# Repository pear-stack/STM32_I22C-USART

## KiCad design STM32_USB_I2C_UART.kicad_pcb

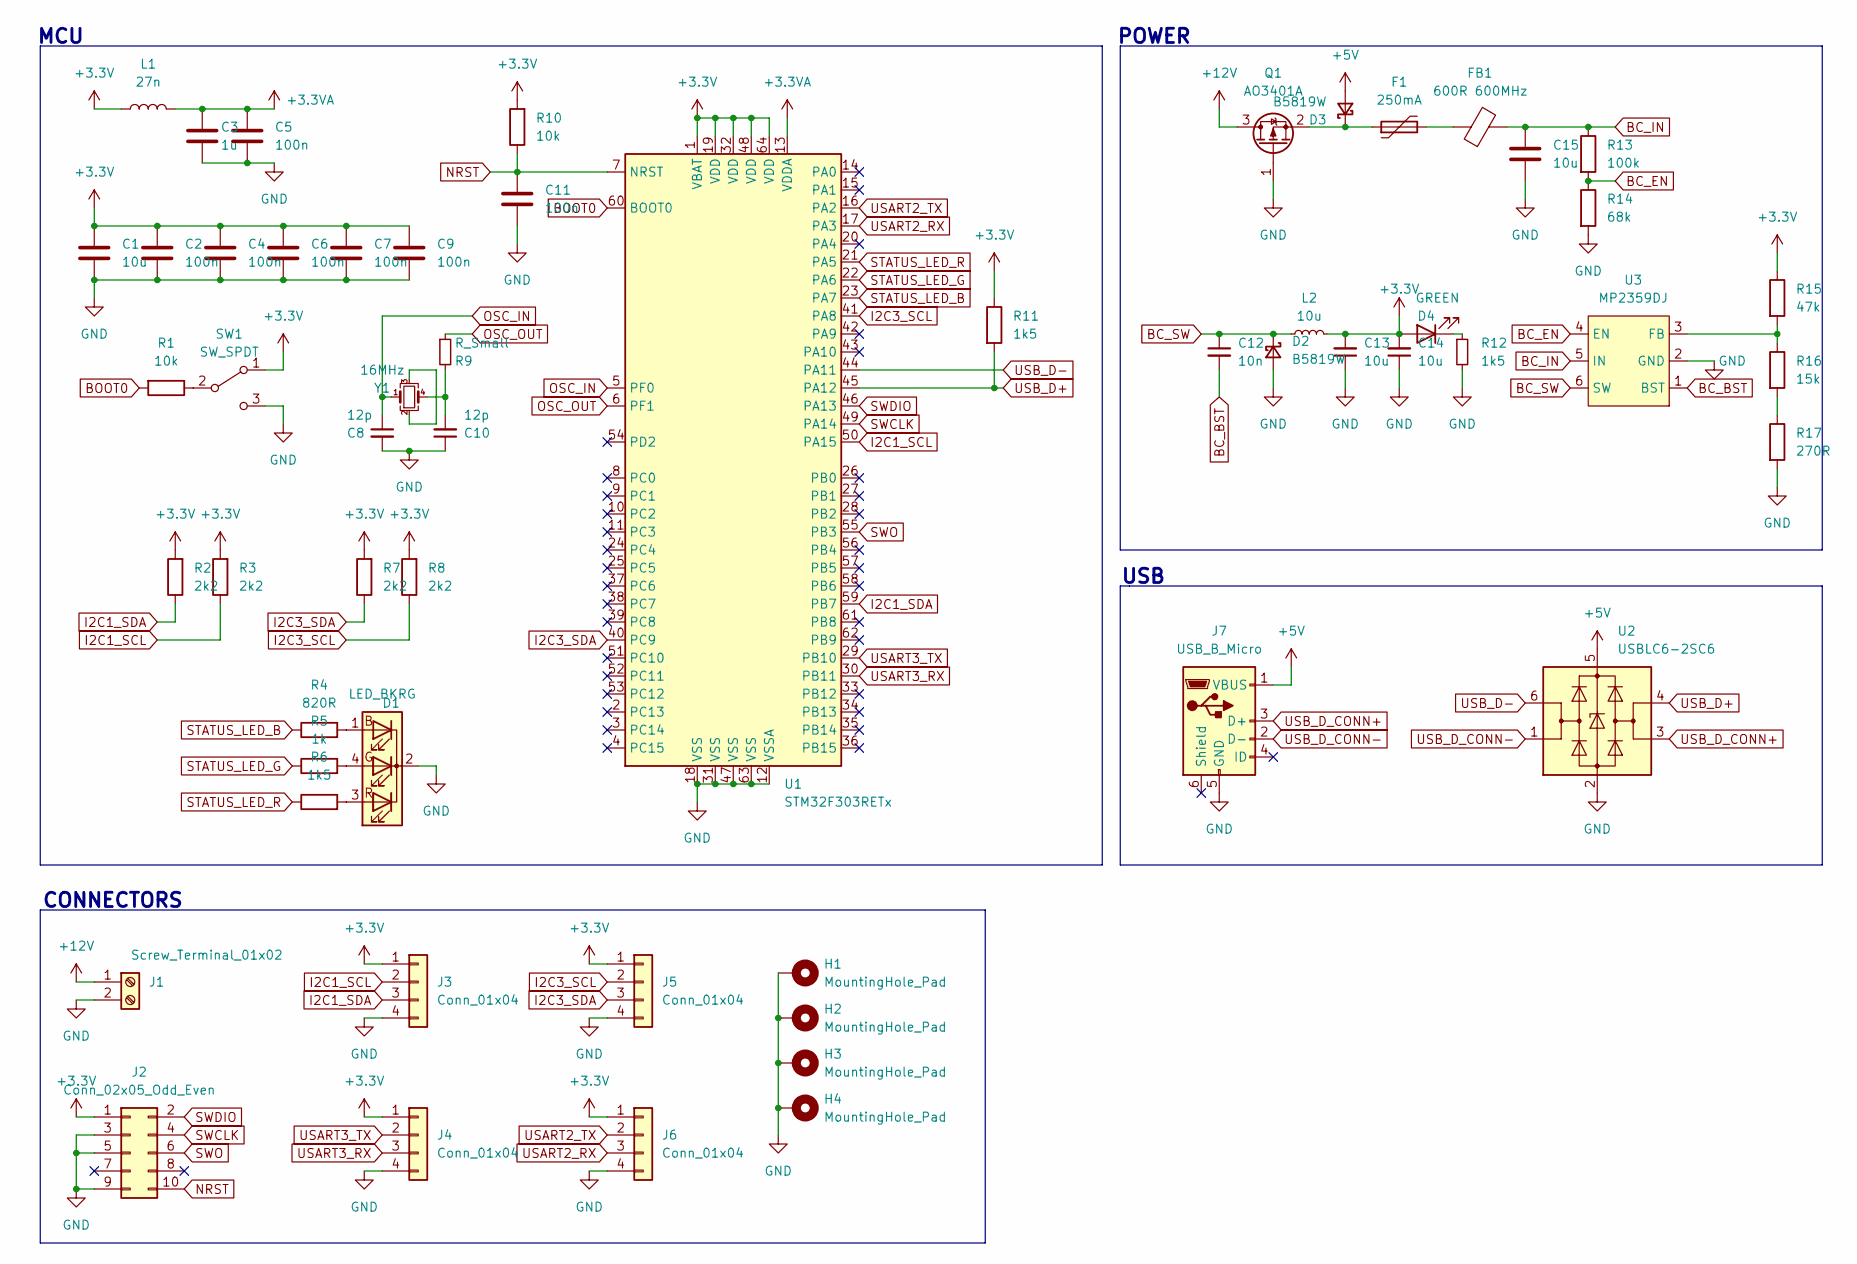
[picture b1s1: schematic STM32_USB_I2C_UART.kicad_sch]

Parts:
C1, C13, C14, C15: 10u; C_0603_1608Metric
C2, C4, C5, C6, C7, C9, C11: 100n; C_0402_1005Metric
C3: 1u; C_0603_1608Metric
C8, C10: 12p; C_0402_1005Metric
C12: 10n; C_0603_1608Metric
D1: LED_BKRG; LED_Inolux_IN-PI554FCH_PLCC4_5.0x5.0mm_P3.2mm
D2, D3: B5819W; D_SOD-123
D4: GREEN; LED_0805_2012Metric
F1: 250mA; Fuse_1206_3216Metric
FB1: 600R 600MHz; L_0805_2012Metric
H1, H2, H3, H4: MountingHole_Pad; MountingHole_4.3mm_M4_Pad_Via
J1: Screw_Terminal_01x02; TerminalBlock_Phoenix_MPT-0,5-2-2.54_1x02_P2.54mm_Horizontal
J2: Conn_02x05_Odd_Even; PinSocket_2x05_P1.27mm_Vertical
J3, J4, J5, J6: Conn_01x04; JST_PH_S4B-PH-K_1x04_P2.00mm_Horizontal
J7: USB_B_Micro; USB_Micro-B_Molex_47346-0001
L1: 27n; L_0402_1005Metric
L2: 10u; L_Sunlord_MWSA0518_5.4x5.2mm
Q1: AO3401A; SOT-23
R1, R10: 10k; R_0402_1005Metric
R2, R3, R7, R8: 2k2; R_0402_1005Metric
R4: 820R; R_0603_1608Metric
R5: 1k; R_0603_1608Metric
R6, R12: 1k5; R_0603_1608Metric
R9: R_Small; R_0402_1005Metric
R11: 1k5; R_0402_1005Metric
R13: 100k; R_0603_1608Metric
R14: 68k; R_0603_1608Metric
R15: 47k; R_0603_1608Metric
R16: 15k; R_0603_1608Metric
R17: 270R; R_0603_1608Metric
SW1: SW_SPDT; SW_DIP_SPSTx01_Slide_Copal_CVS-01xB_W5.9mm_P1mm
U1: STM32F303RETx; LQFP-64_10x10mm_P0.5mm
U2: USBLC6-2SC6; SOT-23-6
U3: MP2359DJ; TSOT-23-6_HandSoldering
Y1: 16MHz; Crystal_SMD_3225-4Pin_3.2x2.5mm

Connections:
+3.3V: C1.1, C2.1, C4.1, C6.1, C7.1, C9.1, C13.2, C14.2, D4.2 (A), J2.1, J3.1, J4.1, J5.1, J6.1, L1.1, L2.2, R2.2, R3.2, R7.2, R8.2, R10.2, R11.1, R15.1, SW1.1 (A), U1.1 (VBAT), U1.19 (VDD), U1.32 (VDD), U1.48 (VDD), U1.64 (VDD)
+3.3VA: C3.1, C5.1, L1.2, U1.13 (VDDA)
+5V: D3.2 (A), J7.1 (VBUS), U2.5 (VBUS)
+12V: J1.1, Q1.3 (D)
BC_BST: C12.2, U3.1 (BST)
BC_EN: R13.2, R14.1, U3.4 (EN)
BC_IN: C15.1, FB1.2, R13.1, U3.5 (IN)
BC_SW: C12.1, D2.1 (K), L2.1, U3.6 (SW)
BOOT0: R1.2, U1.60 (BOOT0)
GND: C1.2, C2.2, C3.2, C4.2, C5.2, C6.2, C7.2, C8.2, C9.2, C10.1, C11.2, C13.1, C14.1, C15.2, D1.2 (K), D2.2 (A), H1.1, H2.1, H3.1, H4.1, J1.2, J2.3, J2.5, J2.9, J3.4, J4.4, J5.4, J6.4, J7.5 (GND), Q1.1 (G), R12.2, R14.2, R17.2, SW1.3 (C), U1.12 (VSSA), U1.18 (VSS), U1.31 (VSS), U1.47 (VSS), U1.63 (VSS), U2.2 (GND), U3.2 (GND)
I2C1_SCL: J3.2, R3.1, U1.50 (PA15)
I2C1_SDA: J3.3, R2.1, U1.59 (PB7)
I2C3_SCL: J5.2, R8.1, U1.41 (PA8)
I2C3_SDA: J5.3, R7.1, U1.40 (PC9)
NRST: C11.1, J2.10, R10.1, U1.7 (NRST)
unnamed: C10.2, R9.2, Y1.4
unnamed: D1.1 (BA), R4.2
unnamed: D1.3 (RA), R6.2
unnamed: D1.4 (GA), R5.2
unnamed: D3.1 (K), F1.1, Q1.2 (S)
unnamed: D4.1 (K), R12.1
unnamed: F1.2, FB1.1
unnamed: R1.1, SW1.2 (B)
unnamed: R15.2, R16.1, U3.3 (FB)
unnamed: R16.2, R17.1
unnamed: Y1.2, Y1.3
OSC_IN: C8.1, U1.5 (PF0), Y1.1
OSC_OUT: R9.1, U1.6 (PF1)
STATUS_LED_B: R4.1, U1.23 (PA7)
STATUS_LED_G: R5.1, U1.22 (PA6)
STATUS_LED_R: R6.1, U1.21 (PA5)
SWCLK: J2.4, U1.49 (PA14)
SWDIO: J2.2, U1.46 (PA13)
SWO: J2.6, U1.55 (PB3)
USART2_RX: J6.3, U1.17 (PA3)
USART2_TX: J6.2, U1.16 (PA2)
USART3_RX: J4.3, U1.30 (PB11)
USART3_TX: J4.2, U1.29 (PB10)
USB_D+: R11.2, U1.45 (PA12), U2.4 (I/O2)
USB_D-: U1.44 (PA11), U2.6 (I/O1)
USB_D_CONN+: J7.3 (D+), U2.3 (I/O2)
USB_D_CONN-: J7.2 (D-), U2.1 (I/O1)

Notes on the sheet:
POWER
USB
MCU
CONNECTORS

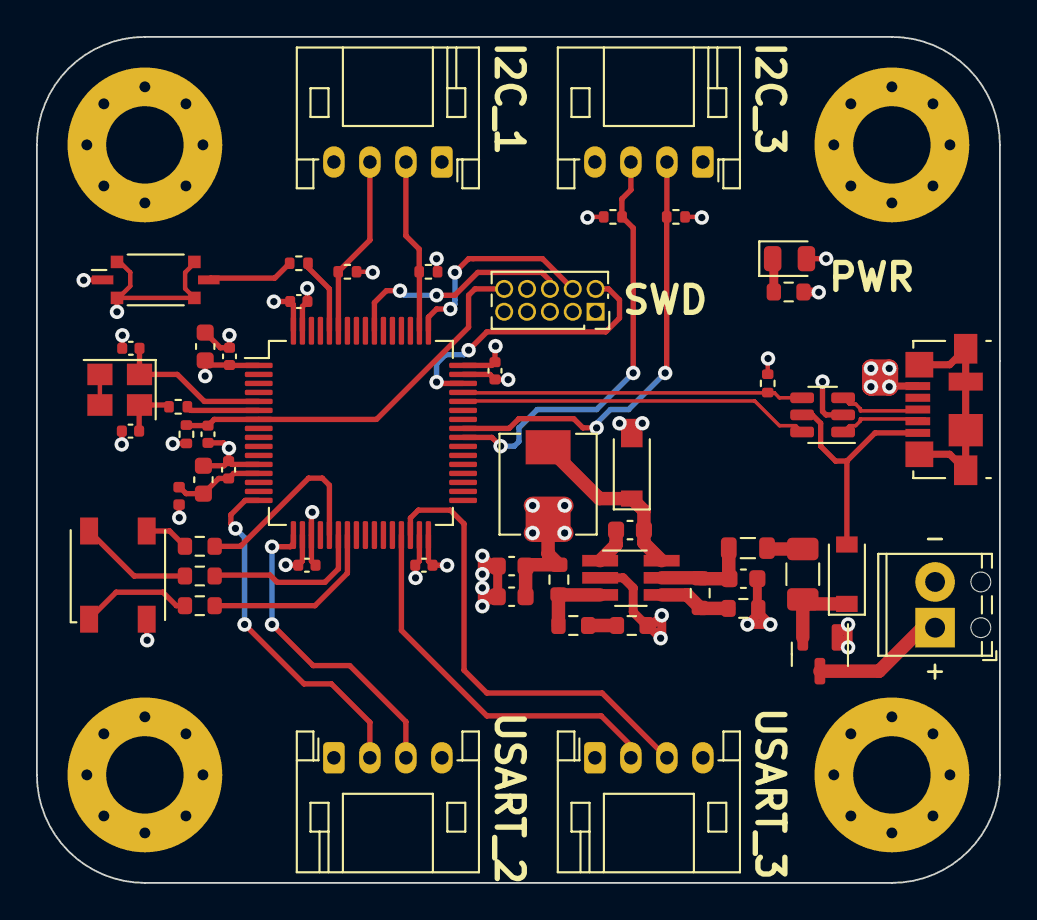
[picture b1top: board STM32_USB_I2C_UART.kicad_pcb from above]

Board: 4 copper layers, 53.5 x 47.0 mm, 57 parts (0 on the bottom side), 42 nets.

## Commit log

2022-12-01 init commit
